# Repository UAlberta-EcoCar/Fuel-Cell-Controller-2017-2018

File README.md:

# Fuel-Cell-Controller-2017-2018

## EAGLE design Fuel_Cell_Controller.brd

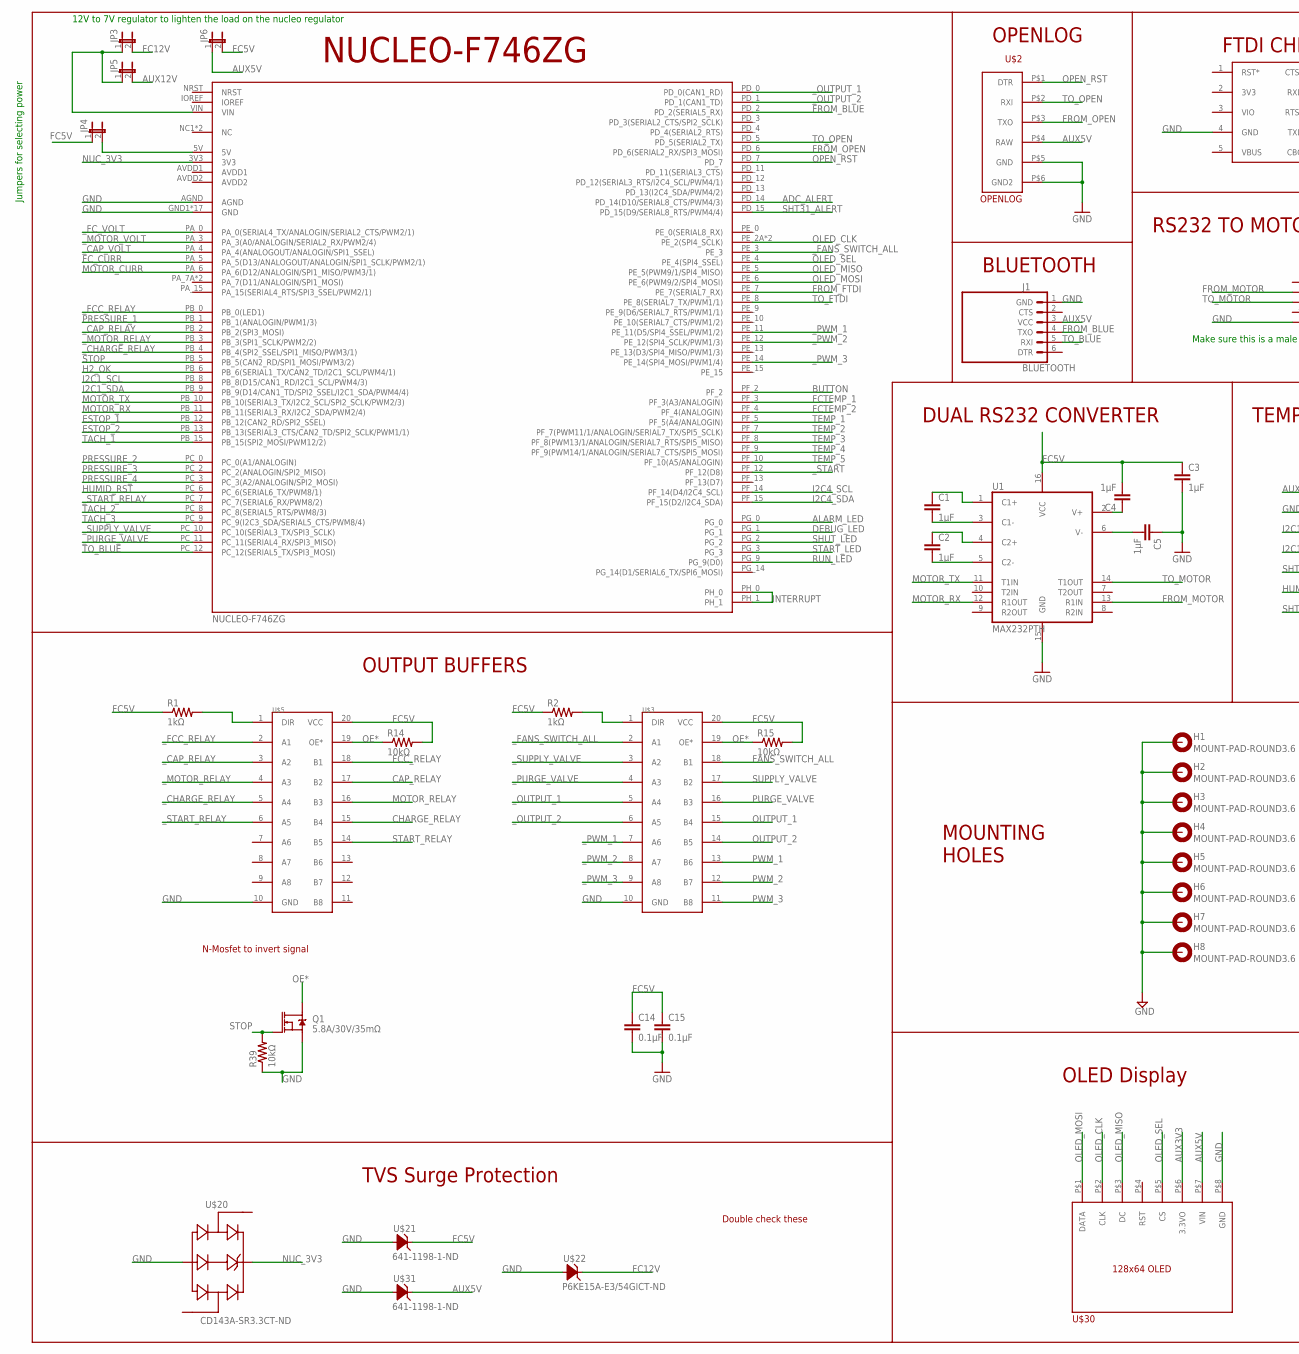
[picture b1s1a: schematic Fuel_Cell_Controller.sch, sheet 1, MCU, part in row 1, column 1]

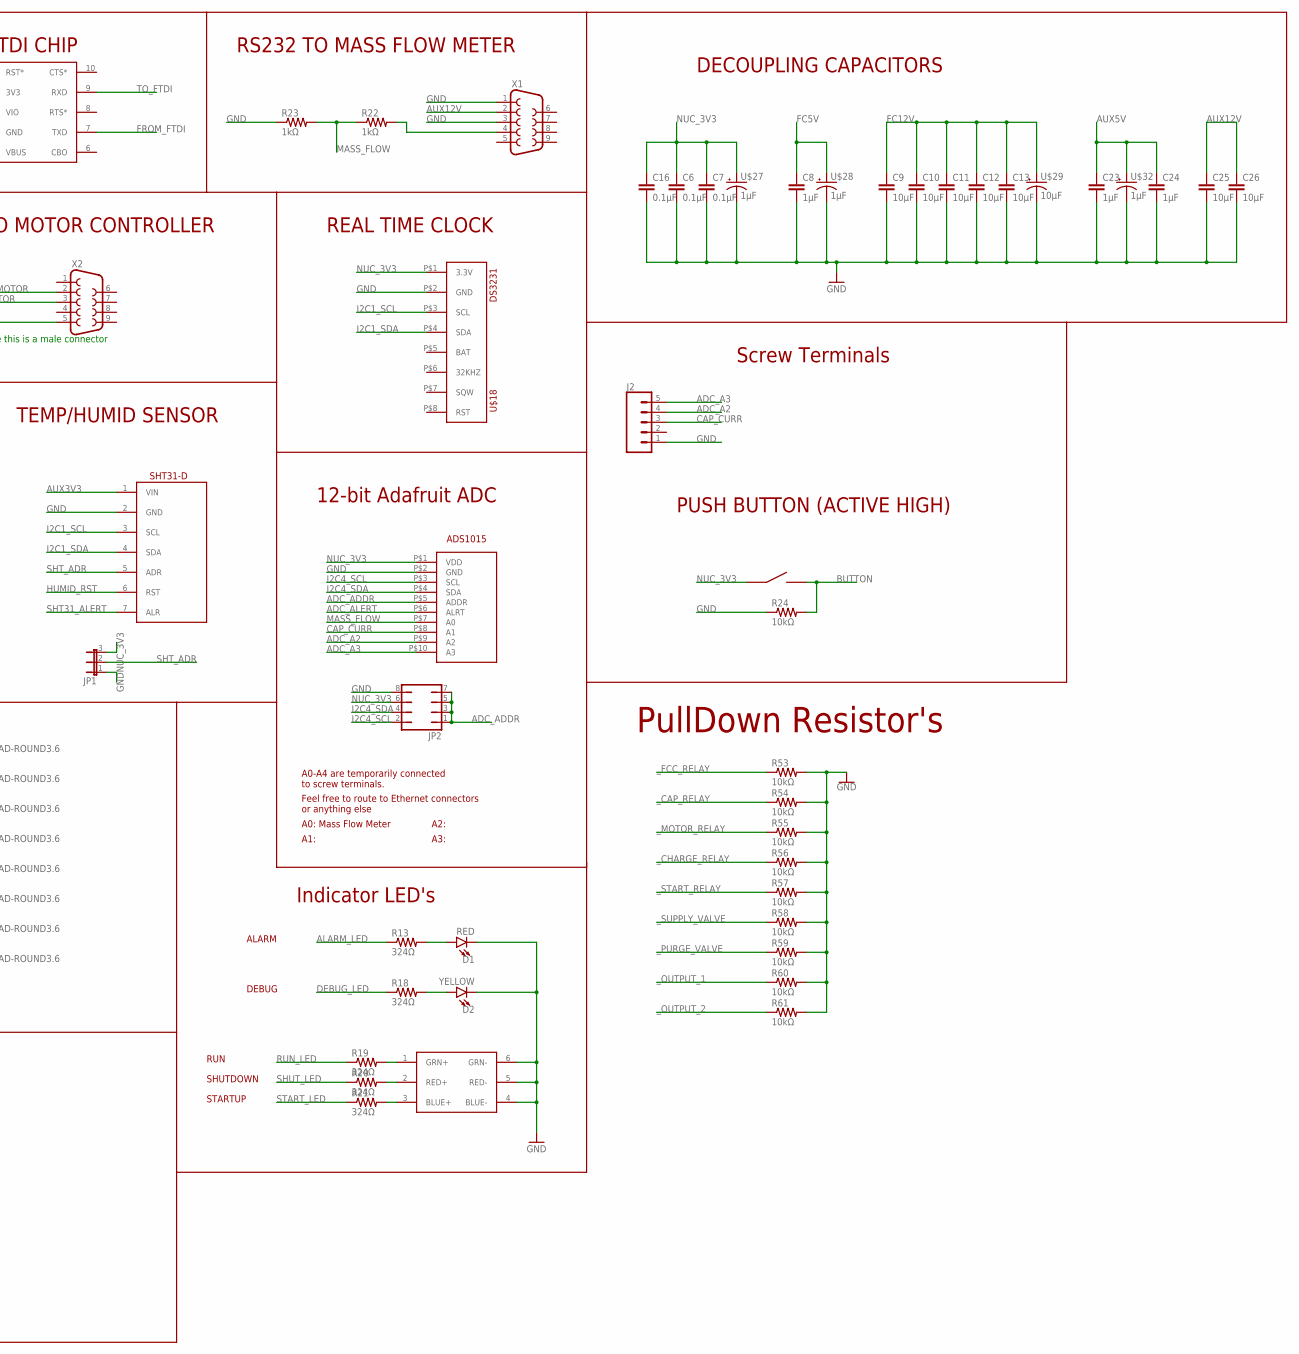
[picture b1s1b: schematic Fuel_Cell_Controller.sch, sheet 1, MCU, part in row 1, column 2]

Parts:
C1, C2, C3, C4, C5, C8, C23, C24: 1µF; 0805
C6, C7, C14, C15, C16: 0.1µF; 0805
C9, C10, C11, C12, C13, C25, C26: 10µF; 0805
D1: RED; LED-1206
D2: YELLOW; LED-1206
H1, H2, H3, H4, H5, H6, H7, H8: MOUNT-PAD-ROUND3.6; 3,6-PAD
J1: BLUETOOTH; 1X06BLUETOOTH
J2: CONN_05SCREW; SCREWTERMINAL-3.5MM-5
JP1: JP2E; JP2
JP2: JP4Q
JP3, JP4, JP5, JP6: JP1E; JP1
Q1: 5.8A/30V/35mΩ; SOT23-3
R1, R2, R22, R23: 1kΩ; 0805
R13, R18, R19, R20, R21: 324Ω; 0805
R14, R15, R24, R39, R53, R54, R55, R56, R57, R58, R59, R60, R61: 10kΩ; 0805
SHTSENSOR: SHT31-DIS; 1X07-SHT31-DIS
U1: MAX232PTH; DIL16
U$1: NUCLEO-F746ZGNUCLEO-F746ZG; NUCLEO-F746ZG
U$2: OPENLOG
U$3, U$5: SN74LVC245AN; DIL20
U$10: UMFT234XF
U$18: DS3231
U$19: ADS1015
U$20: CD143A-SR3.3CT-ND; SOT143_AVAGO
U$21, U$31: 641-1198-1-ND; SOT23
U$22: P6KE15A-E3/54GICT-ND; DO-204AC
U$25: 5060BRG45060BRG4; 5060BRG4
U$26: EG4621CT-ND
U$27, U$28, U$32: 1µF; PANASONIC_D
U$29: 10µF; PANASONIC_D
U$30: ADAFRUITOLED; 1X08OLED
X1, X2: F09HP

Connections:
ADC_A2: J2.4, U$19.P$9 (A2)
ADC_A3: J2.5, U$19.P$10 (A3)
ADC_ADDR: JP2.1, JP2.3, JP2.5, JP2.7, U$19.P$5 (ADDR)
ADC_ALERT: U$1.PD_14 (PD_14(D10/SERIAL8_CTS/PWM4/3)), U$19.P$6 (ALRT)
ALARM_LED: R13.1, U$1.PG_0
AUX3V3: SHTSENSOR.1 (VIN), U$30.P$6 (3.3VO)
AUX5V: C23.1, C24.1, J1.3 (VCC), JP6.1, U$2.P$4 (RAW), U$30.P$7 (VIN), U$31.C, U$32.+; also elsewhere on the board
AUX12V: C25.1, C26.1, JP5.2, X1.2; also elsewhere on the board
BUTTON: R24.2, U$1.PF_2, U$26.P$3, U$26.P$4
CAP_CURR: J2.3, U$19.P$8 (A1); also elsewhere on the board
CAP_RELAY: U$5.17 (B2); also elsewhere on the board
CHARGE_RELAY: U$5.15 (B4); also elsewhere on the board
DEBUG_LED: R18.1, U$1.PG_1
ESTOP_1: U$1.PB_12 (PB_12(CAN2_RD/SPI2_SSEL)); also elsewhere on the board
ESTOP_2: U$1.PB_13 (PB_13(SERIAL3_CTS/CAN2_TD/SPI2_SCLK/PWM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); also elsewhere on the board
FANS_SWITCH_ALL: U$3.18 (B1); also elsewhere on the board
FC5V: C3.1, C4.2, C8.1, C14.1, C15.1, JP4.1, JP6.2, R1.1, R2.1, R14.2, R15.2, U1.16 (VCC), U$3.20 (VCC), U$5.20 (VCC), U$21.C, U$28.+; also elsewhere on the board
FC12V: C9.1, C10.1, C11.1, C12.1, C13.1, JP3.2, U$22.CATHODE (C), U$29.+; also elsewhere on the board
FCC_RELAY: U$5.18 (B1); also elsewhere on the board
FCTEMP_1: U$1.PF_3 (PF_3(A3/ANALOGIN)); also elsewhere on the board
FCTEMP_2: U$1.PF_4 (PF_4(ANALOGIN)); also elsewhere on the board
FC_CURR: U$1.PA_5 (PA_5(D13/ANALOGOUT/ANALOGIN/SPI1_SCLK/P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); also elsewhere on the board
FROM_BLUE: J1.4 (TXO), U$1.PD_2 (PD_2(SERIAL5_RX))
FROM_FTDI: U$1.PE_7 (PE_7(SERIAL7_RX)), U$10.7 (TXD)
FROM_MOTOR: U1.13 (R1IN), X2.2
FROM_OPEN: U$1.PD_6 (PD_6(SERIAL2_RX/SPI3_MOSI)), U$2.P$3 (TXO)
GND: C3.2, C5.1, C6.2, C7.2, C8.2, C9.2, C10.2, C11.2, C12.2, C13.2, C14.2, C15.2, C16.2, C23.2, C24.2, C25.2, C26.2, D1.C, D2.C, H1.B3,6, H2.B3,6, H3.B3,6, H4.B3,6, H5.B3,6, H6.B3,6, H7.B3,6, H8.B3,6, J1.1 (GND), J2.1, JP1.1, JP2.8, Q1.2 (S), R23.1, R24.1, R39.1, R53.2, R54.2, R55.2, R56.2, R57.2, R58.2, R59.2, R60.2, R61.2, SHTSENSOR.2 (GND), U1.15 (GND), U$1.AGND, U$1.GND1 (GND), U$1.GND2 (GND), U$1.GND3 (GND), U$1.GND4 (GND), U$1.GND5 (GND), U$1.GND6 (GND), U$1.GND7 (GND), U$1.GND8 (GND), U$1.GND9 (GND), U$1.GND10 (GND), U$1.GND11 (GND), U$1.GND12 (GND), U$1.GND13 (GND), U$1.GND14 (GND), U$1.GND15 (GND), U$1.GND16 (GND), U$1.GND17 (GND), U$2.P$5 (GND), U$2.P$6 (GND2), U$3.10 (GND), U$5.10 (GND), U$10.4 (GND), U$18.P$2 (GND), U$19.P$2 (GND), U$20.GND, U$21.A1 (A), U$21.A2 (A), U$22.ANODE (A), U$25.4 (BLUE-), U$25.5 (RED-), U$25.6 (GRN-), U$27.-, U$28.-, U$29.-, U$30.P$8 (GND), U$31.A1 (A), U$31.A2 (A), U$32.-, X1.1, X1.3, X2.5; also elsewhere on the board
H2_OK: U$1.PB_6 (PB_6(SERIAL1_TX/CAN2_TD/I2C1_SCL/PWM4/1)); also elsewhere on the board
HUMID_RST: SHTSENSOR.6 (RST), U$1.PC_6 (PC_6(SERIAL6_TX/PWM8/1))
I2C1_SCL: SHTSENSOR.3 (SCL), U$1.PB_8 (PB_8(D15/CAN1_RD/I2C1_SCL/PWM4/3)), U$18.P$3 (SCL)
I2C1_SDA: SHTSENSOR.4 (SDA), U$1.PB_9 (PB_9(D14/CAN1_TD/SPI2_SSEL/I2C1_SDA/PWM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), U$18.P$4 (SDA)
I2C4_SCL: JP2.2, U$1.PF_14 (PF_14(D4/I2C4_SCL)), U$19.P$3 (SCL)
I2C4_SDA: JP2.4, U$1.PF_15 (PF_15(D2/I2C4_SDA)), U$19.P$4 (SDA)
INTERRUPT: U$1.PH_0, U$1.PH_1
MASS_FLOW: R22.1, R23.2, U$19.P$7 (A0)
MOTOR_CURR: U$1.PA_6 (PA_6(D12/ANALOGIN/SPI1_MISO/PWM3/1)); also elsewhere on the board
MOTOR_RELAY: U$5.16 (B3); also elsewhere on the board
MOTOR_RX: U1.12 (R1OUT), U$1.PB_11 (PB_11(SERIAL3_RX/I2C2_SDA/PWM2/4))
MOTOR_TX: U1.11 (T1IN), U$1.PB_10 (PB_10(SERIAL3_TX/I2C2_SCL/SPI2_SCLK/PWM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)
unnamed: JP4.2, U$1.5V
unnamed: C1.1, U1.1 (C1+)
unnamed: C1.2, U1.3 (C1-)
unnamed: C2.1, U1.4 (C2+)
unnamed: C2.2, U1.5 (C2-)
unnamed: C4.1, U1.2 (V+)
unnamed: C5.2, U1.6 (V-)
unnamed: R2.2, U$3.1 (DIR)
unnamed: R1.2, U$5.1 (DIR)
unnamed: R22.2, X1.4
unnamed: D1.A, R13.2
unnamed: D2.A, R18.2
unnamed: R19.2, U$25.1 (GRN+)
unnamed: R20.2, U$25.2 (RED+)
unnamed: R21.2, U$25.3 (BLUE+)
NUC_3V3: C6.1, C7.1, C16.1, JP1.3, JP2.6, U$1.3V3, U$18.P$1 (3.3V), U$19.P$1 (VDD), U$20.VDD, U$26.P$1, U$26.P$2, U$27.+; also elsewhere on the board
OE*: Q1.3 (D), R14.1, R15.1, U$3.19 (OE*), U$5.19 (OE*)
OLED_CLK: U$1.PE_2A (PE_2(SPI4_SCLK)), U$1.PE_2B (PE_2(SPI4_SCLK)), U$30.P$2 (CLK)
OLED_MISO: U$1.PE_5 (PE_5(PWM9/1/SPI4_MISO)), U$30.P$3 (DC)
OLED_MOSI: U$1.PE_6 (PE_6(PWM9/2/SPI4_MOSI)), U$30.P$1 (DATA)
OLED_SEL: U$1.PE_4 (PE_4(SPI4_SSEL)), U$30.P$5 (CS)
OPEN_RST: U$1.PD_7, U$2.P$1 (DTR)
OUTPUT_1: U$3.15 (B4); also elsewhere on the board
OUTPUT_2: U$3.14 (B5); also elsewhere on the board
PRESSURE_1: U$1.PB_1 (PB_1(ANALOGIN/PWM1/3)); also elsewhere on the board
PRESSURE_2: U$1.PC_0 (PC_0(A1/ANALOGIN)); also elsewhere on the board
PRESSURE_3: U$1.PC_2 (PC_2(ANALOGIN/SPI2_MISO)); also elsewhere on the board
PRESSURE_4: U$1.PC_3 (PC_3(A2/ANALOGIN/SPI2_MOSI)); also elsewhere on the board
PURGE_VALVE: U$3.16 (B3); also elsewhere on the board
PWM_1: U$3.13 (B6); also elsewhere on the board
PWM_2: U$3.12 (B7); also elsewhere on the board
PWM_3: U$3.11 (B8); also elsewhere on the board
RUN_LED: R19.1, U$1.PG_9 (PG_9(D0))
SHT31_ALERT: SHTSENSOR.7 (ALR), U$1.PD_15 (PD_15(D9/SERIAL8_RTS/PWM4/4))
SHT_ADR: JP1.2, SHTSENSOR.5 (ADR)
SHUT_LED: R20.1, U$1.PG_2
START_LED: R21.1, U$1.PG_3
START_RELAY: U$5.14 (B5); also elsewhere on the board
STOP: Q1.1 (G), R39.2, U$1.PB_5 (PB_5(CAN2_RD/SPI1_MOSI/PWM3/2)); also elsewhere on the board
SUPPLY_VALVE: U$3.17 (B2); also elsewhere on the board
TACH_1: U$1.PB_15 (PB_15(SPI2_MOSI/PWM12/2)); also elsewhere on the board
TACH_2: U$1.PC_8 (PC_8(SERIAL5_RTS/PWM8/3)); also elsewhere on the board
TACH_3: U$1.PC_9 (PC_9(I2C3_SDA/SERIAL5_CTS/PWM8/4)); also elsewhere on the board
TEMP_1: U$1.PF_5 (PF_5(A4/ANALOGIN)); also elsewhere on the board
TEMP_2: U$1.PF_7 (PF_7(PWM11/1/ANALOGIN/SERIAL7_TX/SPI5_S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); also elsewhere on the board
TEMP_3: U$1.PF_8 (PF_8(PWM13/1/ANALOGIN/SERIAL7_RTS/SPI5_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); also elsewhere on the board
TEMP_4: U$1.PF_9 (PF_9(PWM14/1/ANALOGIN/SERIAL7_CTS/SPI5_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); also elsewhere on the board
TEMP_5: U$1.PF_10 (PF_10(A5/ANALOGIN)); also elsewhere on the board
TO_BLUE: J1.5 (RXI), U$1.PC_12 (PC_12(SERIAL5_TX/SPI3_MOSI))
TO_FTDI: U$1.PE_8 (PE_8(SERIAL7_TX/PWM1/1)), U$10.9 (RXD)
TO_MOTOR: U1.14 (T1OUT), X2.3
TO_OPEN: U$1.PD_5 (PD_5(SERIAL2_TX)), U$2.P$2 (RXI)
VIN: JP3.1, JP5.1, U$1.VIN
_CAP_RELAY: R54.1, U$1.PB_2 (PB_2(SPI3_MOSI)), U$5.3 (A2)
_CAP_VOLT: U$1.PA_4 (PA_4(ANALOGOUT/ANALOGIN/SPI1_SSEL)); also elsewhere on the board
_CHARGE_RELAY: R56.1, U$1.PB_4 (PB_4(SPI2_SSEL/SPI1_MISO/PWM3/1)), U$5.5 (A4)
_FANS_SWITCH_ALL: U$1.PE_3, U$3.2 (A1)
_FCC_RELAY: R53.1, U$1.PB_0 (PB_0(LED1)), U$5.2 (A1)
_FC_VOLT: U$1.PA_0 (PA_0(SERIAL4_TX/ANALOGIN/SERIAL2_CTS/PW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); also elsewhere on the board
_MOTOR_RELAY: R55.1, U$1.PB_3 (PB_3(SPI1_SCLK/PWM2/2)), U$5.4 (A3)
_MOTOR_VOLT: U$1.PA_3 (PA_3(A0/ANALOGIN/SERIAL2_RX/PWM2/4)); also elsewhere on the board
_OUTPUT_1: R60.1, U$1.PD_0 (PD_0(CAN1_RD)), U$3.5 (A4)
_OUTPUT_2: R61.1, U$1.PD_1 (PD_1(CAN1_TD)), U$3.6 (A5)
_PURGE_VALVE: R59.1, U$1.PC_11 (PC_11(SERIAL4_RX/SPI3_MISO)), U$3.4 (A3)
_PWM_1: U$1.PE_11 (PE_11(D5/SPI4_SSEL/PWM1/2)), U$3.7 (A6)
_PWM_2: U$1.PE_12 (PE_12(SPI4_SCLK/PWM1/3)), U$3.8 (A7)
_PWM_3: U$1.PE_14 (PE_14(SPI4_MOSI/PWM1/4)), U$3.9 (A8)
_START: U$1.PF_12 (PF_12(D8)); also elsewhere on the board
_START_RELAY: R57.1, U$1.PC_7 (PC_7(SERIAL6_RX/PWM8/2)), U$5.6 (A5)
_SUPPLY_VALVE: R58.1, U$1.PC_10 (PC_10(SERIAL3_TX/SPI3_SCLK)), U$3.3 (A2)

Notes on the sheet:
NUCLEO-F746ZG
OPENLOG
BLUETOOTH
DUAL RS232 CONVERTER
RS232 TO MOTOR CONTROLLER
FTDI CHIP
TEMP/HUMID SENSOR
RS232 TO MASS FLOW METER
REAL TIME CLOCK
OUTPUT BUFFERS
12-bit Adafruit ADC
A0-A4 are temporarily connected to screw terminals.
Feel free to route to Ethernet connectors or anything else
A0: Mass Flow Meter
A1:
A2:
A3:
MOUNTING HOLES
Indicator LED's
TVS Surge Protection
DECOUPLING CAPACITORS
ALARM
Double check these
Screw Terminals
DEBUG
RUN
SHUTDOWN
STARTUP
PUSH BUTTON (ACTIVE HIGH)
OLED Display
N-Mosfet to invert signal
Jumpers for selecting power
12V to 7V regulator to lighten the load on the nucleo regulator
Make sure this is a male connector
PullDown Resistor's

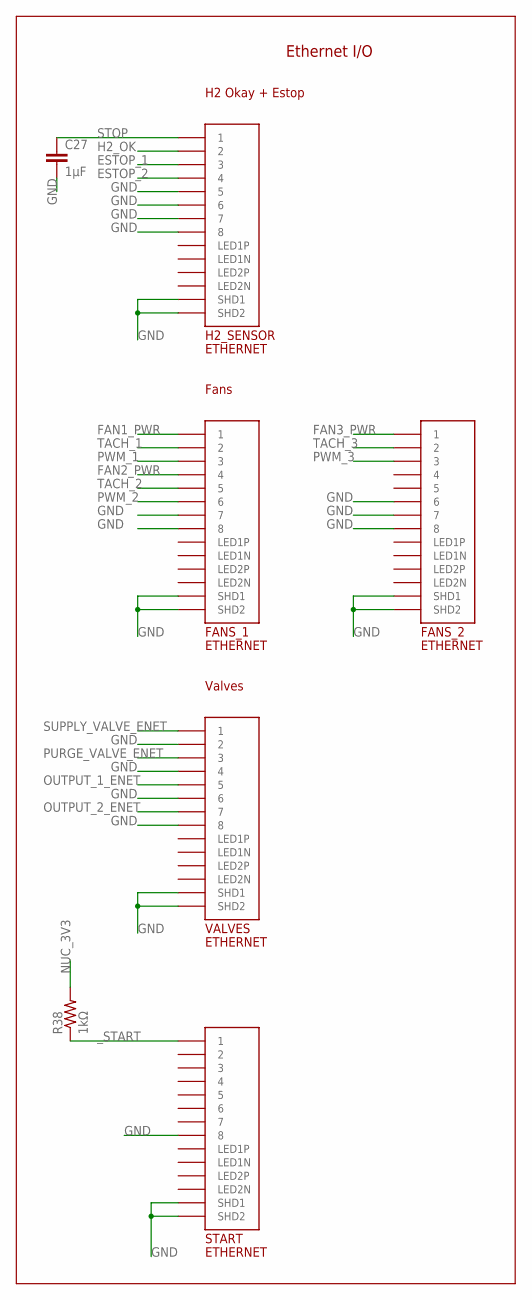
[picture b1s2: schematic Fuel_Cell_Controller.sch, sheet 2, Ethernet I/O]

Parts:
C27: 1µF; 0805
FANS_1, FANS_2: ETHERNET; A122645-ND
H2_SENSOR: ETHERNET; A122645-ND
R38: 1kΩ; 0805
START: ETHERNET; A122645-ND
VALVES: ETHERNET; A122645-ND

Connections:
ESTOP_1: H2_SENSOR.P$3 (3); also elsewhere on the board
ESTOP_2: H2_SENSOR.P$4 (4); also elsewhere on the board
FAN1_PWR: FANS_1.P$1 (1); also elsewhere on the board
FAN2_PWR: FANS_1.P$4 (4); also elsewhere on the board
FAN3_PWR: FANS_2.P$1 (1); also elsewhere on the board
GND: C27.2, FANS_1.P$7 (7), FANS_1.P$8 (8), FANS_1.P$13 (SHD1), FANS_1.P$14 (SHD2), FANS_2.P$6 (6), FANS_2.P$7 (7), FANS_2.P$8 (8), FANS_2.P$13 (SHD1), FANS_2.P$14 (SHD2), H2_SENSOR.P$5 (5), H2_SENSOR.P$6 (6), H2_SENSOR.P$7 (7), H2_SENSOR.P$8 (8), H2_SENSOR.P$13 (SHD1), H2_SENSOR.P$14 (SHD2), START.P$8 (8), START.P$13 (SHD1), START.P$14 (SHD2), VALVES.P$2 (2), VALVES.P$4 (4), VALVES.P$6 (6), VALVES.P$8 (8), VALVES.P$13 (SHD1), VALVES.P$14 (SHD2); also elsewhere on the board
H2_OK: H2_SENSOR.P$2 (2); also elsewhere on the board
NUC_3V3: R38.2; also elsewhere on the board
OUTPUT_1_ENET: VALVES.P$5 (5); also elsewhere on the board
OUTPUT_2_ENET: VALVES.P$7 (7); also elsewhere on the board
PURGE_VALVE_ENET: VALVES.P$3 (3); also elsewhere on the board
PWM_1: FANS_1.P$3 (3); also elsewhere on the board
PWM_2: FANS_1.P$6 (6); also elsewhere on the board
PWM_3: FANS_2.P$3 (3); also elsewhere on the board
STOP: C27.1, H2_SENSOR.P$1 (1); also elsewhere on the board
SUPPLY_VALVE_ENET: VALVES.P$1 (1); also elsewhere on the board
TACH_1: FANS_1.P$2 (2); also elsewhere on the board
TACH_2: FANS_1.P$5 (5); also elsewhere on the board
TACH_3: FANS_2.P$2 (2); also elsewhere on the board
_START: R38.1, START.P$1 (1); also elsewhere on the board

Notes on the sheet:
Ethernet I/O
Fans
Valves
H2 Okay + Estop

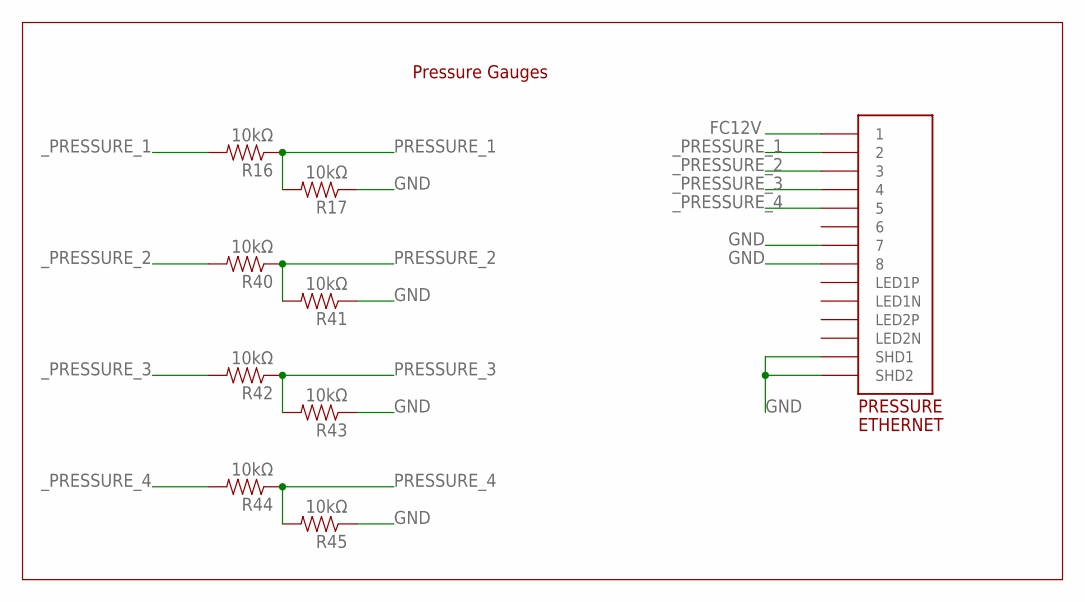
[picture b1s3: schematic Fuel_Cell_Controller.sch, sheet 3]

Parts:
PRESSURE: ETHERNET; A122645-ND
R16, R17, R40, R41, R42, R43, R44, R45: 10kΩ; 0805

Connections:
FC12V: PRESSURE.P$1 (1); also elsewhere on the board
GND: PRESSURE.P$7 (7), PRESSURE.P$8 (8), PRESSURE.P$13 (SHD1), PRESSURE.P$14 (SHD2), R17.1, R41.1, R43.1, R45.1; also elsewhere on the board
PRESSURE_1: R16.1, R17.2; also elsewhere on the board
PRESSURE_2: R40.1, R41.2; also elsewhere on the board
PRESSURE_3: R42.1, R43.2; also elsewhere on the board
PRESSURE_4: R44.1, R45.2; also elsewhere on the board
_PRESSURE_1: PRESSURE.P$2 (2), R16.2
_PRESSURE_2: PRESSURE.P$3 (3), R40.2
_PRESSURE_3: PRESSURE.P$4 (4), R42.2
_PRESSURE_4: PRESSURE.P$5 (5), R44.2

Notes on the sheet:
Pressure Gauges

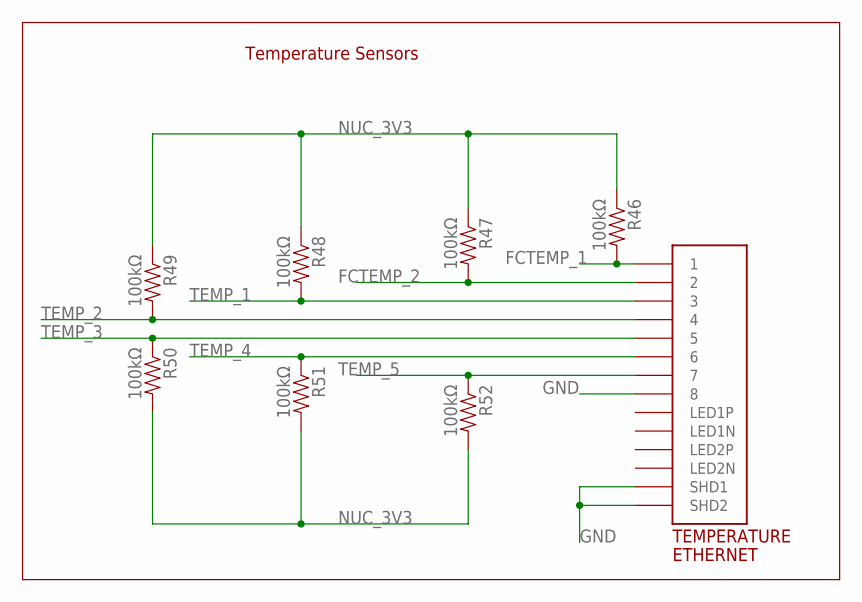
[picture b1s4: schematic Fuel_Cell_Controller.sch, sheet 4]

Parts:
R46, R47, R48, R49, R50, R51, R52: 100kΩ; 0805
TEMPERATURE: ETHERNET; A122645-ND

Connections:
FCTEMP_1: R46.2, TEMPERATURE.P$1 (1); also elsewhere on the board
FCTEMP_2: R47.2, TEMPERATURE.P$2 (2); also elsewhere on the board
GND: TEMPERATURE.P$8 (8), TEMPERATURE.P$13 (SHD1), TEMPERATURE.P$14 (SHD2); also elsewhere on the board
NUC_3V3: R46.1, R47.1, R48.1, R49.1, R50.2, R51.2, R52.2; also elsewhere on the board
TEMP_1: R48.2, TEMPERATURE.P$3 (3); also elsewhere on the board
TEMP_2: R49.2, TEMPERATURE.P$4 (4); also elsewhere on the board
TEMP_3: R50.1, TEMPERATURE.P$5 (5); also elsewhere on the board
TEMP_4: R51.1, TEMPERATURE.P$6 (6); also elsewhere on the board
TEMP_5: R52.1, TEMPERATURE.P$7 (7); also elsewhere on the board

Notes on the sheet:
Temperature Sensors

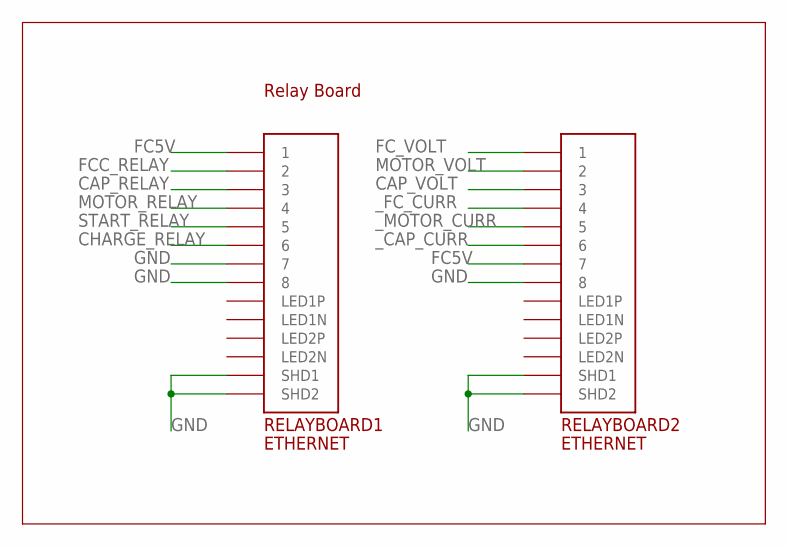
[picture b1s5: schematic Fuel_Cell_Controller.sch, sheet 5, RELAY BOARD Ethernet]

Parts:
RELAYBOARD1, RELAYBOARD2: ETHERNET; A122645-ND

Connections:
CAP_RELAY: RELAYBOARD1.P$3 (3); also elsewhere on the board
CAP_VOLT: RELAYBOARD2.P$3 (3); also elsewhere on the board
CHARGE_RELAY: RELAYBOARD1.P$6 (6); also elsewhere on the board
FC5V: RELAYBOARD1.P$1 (1), RELAYBOARD2.P$7 (7); also elsewhere on the board
FCC_RELAY: RELAYBOARD1.P$2 (2); also elsewhere on the board
FC_VOLT: RELAYBOARD2.P$1 (1); also elsewhere on the board
GND: RELAYBOARD1.P$7 (7), RELAYBOARD1.P$8 (8), RELAYBOARD1.P$13 (SHD1), RELAYBOARD1.P$14 (SHD2), RELAYBOARD2.P$8 (8), RELAYBOARD2.P$13 (SHD1), RELAYBOARD2.P$14 (SHD2); also elsewhere on the board
MOTOR_RELAY: RELAYBOARD1.P$4 (4); also elsewhere on the board
MOTOR_VOLT: RELAYBOARD2.P$2 (2); also elsewhere on the board
START_RELAY: RELAYBOARD1.P$5 (5); also elsewhere on the board
_CAP_CURR: RELAYBOARD2.P$6 (6); also elsewhere on the board
_FC_CURR: RELAYBOARD2.P$4 (4); also elsewhere on the board
_MOTOR_CURR: RELAYBOARD2.P$5 (5); also elsewhere on the board

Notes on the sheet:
Relay Board

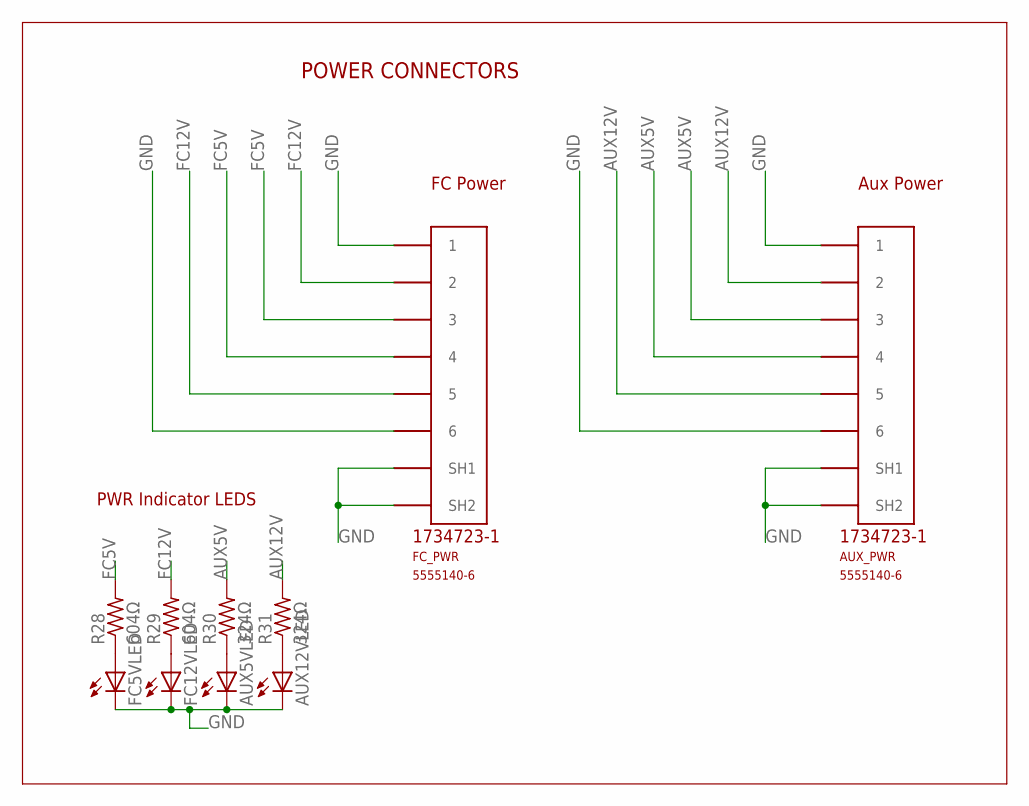
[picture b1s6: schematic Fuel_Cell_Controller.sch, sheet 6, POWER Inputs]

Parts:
AUX5VLED, AUX12VLED: LEDCHIP-LED0805; CHIP-LED0805
AUX_PWR: 5555140-6; 1734723-1_RJ11
FC5VLED, FC12VLED: LEDCHIP-LED0805; CHIP-LED0805
FC_PWR: 5555140-6; 1734723-1_RJ11
R28, R29: 604Ω; R0805
R30, R31: 324Ω; R0805

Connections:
AUX5V: AUX_PWR.3, AUX_PWR.4, R30.2; also elsewhere on the board
AUX12V: AUX_PWR.2, AUX_PWR.5, R31.2; also elsewhere on the board
FC5V: FC_PWR.3, FC_PWR.4, R28.2; also elsewhere on the board
FC12V: FC_PWR.2, FC_PWR.5, R29.2; also elsewhere on the board
GND: AUX5VLED.C, AUX12VLED.C, AUX_PWR.1, AUX_PWR.6, AUX_PWR.SH1, AUX_PWR.SH2, FC5VLED.C, FC12VLED.C, FC_PWR.1, FC_PWR.6, FC_PWR.SH1, FC_PWR.SH2; also elsewhere on the board
unnamed: FC5VLED.A, R28.1
unnamed: FC12VLED.A, R29.1
unnamed: AUX5VLED.A, R30.1
unnamed: AUX12VLED.A, R31.1

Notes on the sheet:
FC Power
Aux Power
POWER CONNECTORS
PWR Indicator LEDS

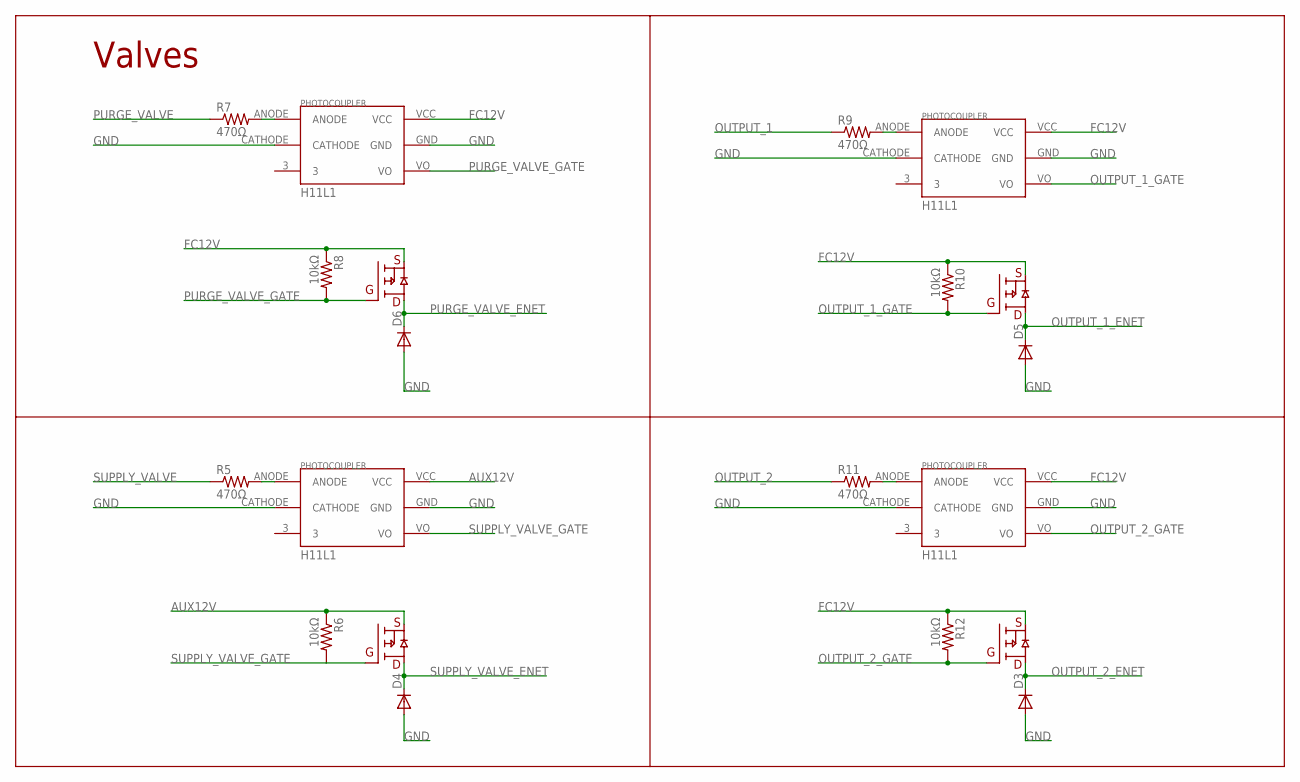
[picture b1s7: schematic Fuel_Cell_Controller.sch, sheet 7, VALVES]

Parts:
D3, D4, D5, D6: DIODE-DO214AC; DO214AC
R5, R7, R9, R11: 470Ω; 0805
R6, R8, R10, R12: 10kΩ; 0805
U$6, U$11, U$14, U$16: H11L1H11L1; H11L1
U$12, U$13, U$15, U$17: DMP3056L-7DMP3056L-7; DMP3056L-7

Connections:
AUX12V: R6.1, U$6.VCC, U$12.S (SOURCE); also elsewhere on the board
FC12V: R8.1, R10.1, R12.1, U$11.VCC, U$13.S (SOURCE), U$14.VCC, U$15.S (SOURCE), U$16.VCC, U$17.S (SOURCE); also elsewhere on the board
GND: D3.A, D4.A, D5.A, D6.A, U$6.CATHODE, U$6.GND, U$11.CATHODE, U$11.GND, U$14.CATHODE, U$14.GND, U$16.CATHODE, U$16.GND; also elsewhere on the board
unnamed: R5.2, U$6.ANODE
unnamed: R7.2, U$11.ANODE
unnamed: R9.2, U$14.ANODE
unnamed: R11.2, U$16.ANODE
OUTPUT_1: R9.1; also elsewhere on the board
OUTPUT_1_ENET: D5.C, U$15.D (DRAIN); also elsewhere on the board
OUTPUT_1_GATE: R10.2, U$14.VO, U$15.G (GATE)
OUTPUT_2: R11.1; also elsewhere on the board
OUTPUT_2_ENET: D3.C, U$17.D (DRAIN); also elsewhere on the board
OUTPUT_2_GATE: R12.2, U$16.VO, U$17.G (GATE)
PURGE_VALVE: R7.1; also elsewhere on the board
PURGE_VALVE_ENET: D6.C, U$13.D (DRAIN); also elsewhere on the board
PURGE_VALVE_GATE: R8.2, U$11.VO, U$13.G (GATE)
SUPPLY_VALVE: R5.1; also elsewhere on the board
SUPPLY_VALVE_ENET: D4.C, U$12.D (DRAIN); also elsewhere on the board
SUPPLY_VALVE_GATE: R6.2, U$6.VO, U$12.G (GATE)

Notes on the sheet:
Valves

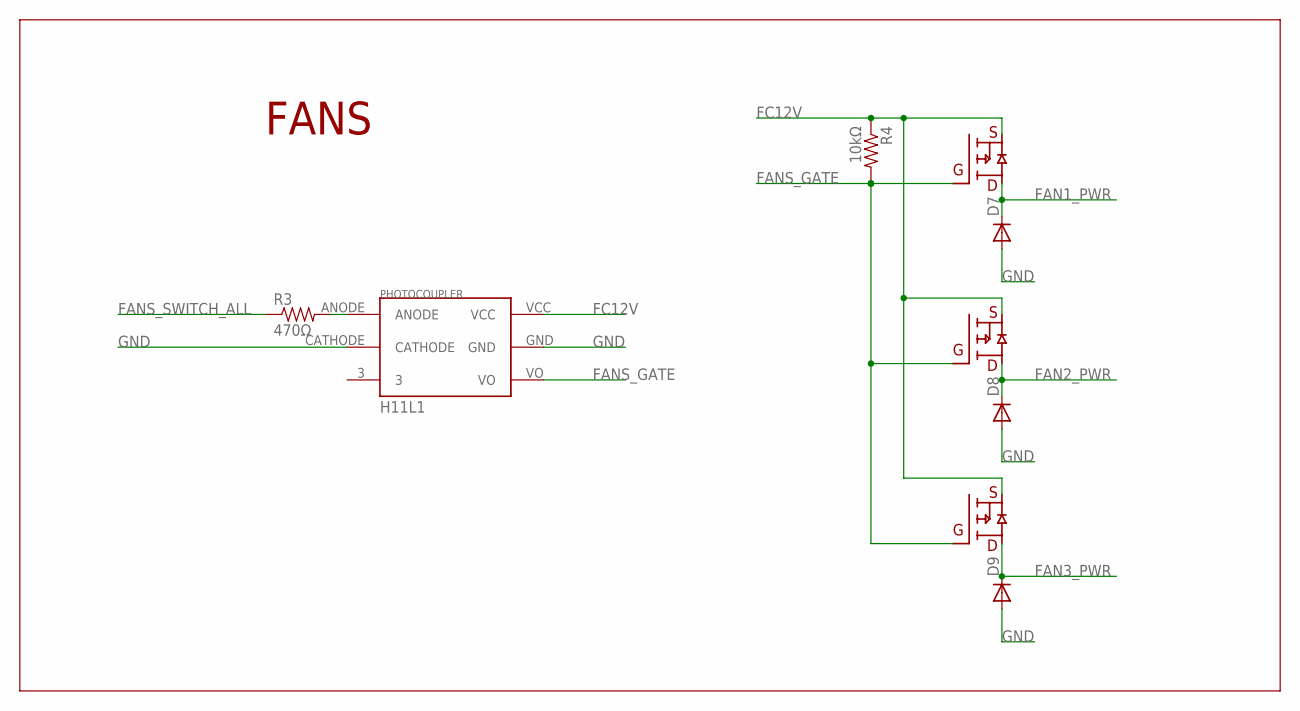
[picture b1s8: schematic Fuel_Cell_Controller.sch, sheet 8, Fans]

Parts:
D7, D8, D9: DIODE-DO214AC; DO214AC
R3: 470Ω; 0805
R4: 10kΩ; 0805
U$4: H11L1H11L1; H11L1
U$7, U$8, U$9: DMP3056L-7DMP3056L-7; DMP3056L-7

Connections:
FAN1_PWR: D7.C, U$7.D (DRAIN); also elsewhere on the board
FAN2_PWR: D8.C, U$8.D (DRAIN); also elsewhere on the board
FAN3_PWR: D9.C, U$9.D (DRAIN); also elsewhere on the board
FANS_GATE: R4.2, U$4.VO, U$7.G (GATE), U$8.G (GATE), U$9.G (GATE)
FANS_SWITCH_ALL: R3.1; also elsewhere on the board
FC12V: R4.1, U$4.VCC, U$7.S (SOURCE), U$8.S (SOURCE), U$9.S (SOURCE); also elsewhere on the board
GND: D7.A, D8.A, D9.A, U$4.CATHODE, U$4.GND; also elsewhere on the board
unnamed: R3.2, U$4.ANODE

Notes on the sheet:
FANS

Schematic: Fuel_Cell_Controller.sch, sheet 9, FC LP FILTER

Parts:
C17, C18, C19, C20, C21, C22: CAP0805; 0805
LP_FILTER_OP_AMP: TLV2404TLV2404; DIL14
R25, R26, R27: 0402
R32, R33, R34, R35, R36, R37: R-US_R0805; R0805

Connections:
CAP_CURR: C17.1, R36.2, R37.1; also elsewhere on the board
CAP_VOLT: LP_FILTER_OP_AMP.10 (3IN+); also elsewhere on the board
FC5V: LP_FILTER_OP_AMP.4 (VCC); also elsewhere on the board
FC_CURR: C19.1, R32.2, R33.1; also elsewhere on the board
FC_VOLT: LP_FILTER_OP_AMP.3 (1IN+); also elsewhere on the board
GND: C17.2, C18.2, C19.2, C20.2, C21.2, C22.2, LP_FILTER_OP_AMP.11 (GND), LP_FILTER_OP_AMP.12 (4IN+), LP_FILTER_OP_AMP.13 (4IN-), R33.2, R35.2, R37.2; also elsewhere on the board
MOTOR_CURR: C18.1, R34.2, R35.1; also elsewhere on the board
MOTOR_VOLT: LP_FILTER_OP_AMP.5 (2IN+); also elsewhere on the board
unnamed: LP_FILTER_OP_AMP.1 (1OUT), LP_FILTER_OP_AMP.2 (1IN-), R25.2
unnamed: LP_FILTER_OP_AMP.6 (2IN-), LP_FILTER_OP_AMP.7 (2OUT), R26.2
unnamed: LP_FILTER_OP_AMP.8 (3OUT), LP_FILTER_OP_AMP.9 (3IN-), R27.1
_CAP_CURR: R36.1; also elsewhere on the board
_CAP_VOLT: C22.1, R27.2; also elsewhere on the board
_FC_CURR: R32.1; also elsewhere on the board
_FC_VOLT: C20.1, R25.1; also elsewhere on the board
_MOTOR_CURR: R34.1; also elsewhere on the board
_MOTOR_VOLT: C21.1, R26.1; also elsewhere on the board

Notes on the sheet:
Current Sensors LP Filter and Voltage Divider
Voltages LP Filter

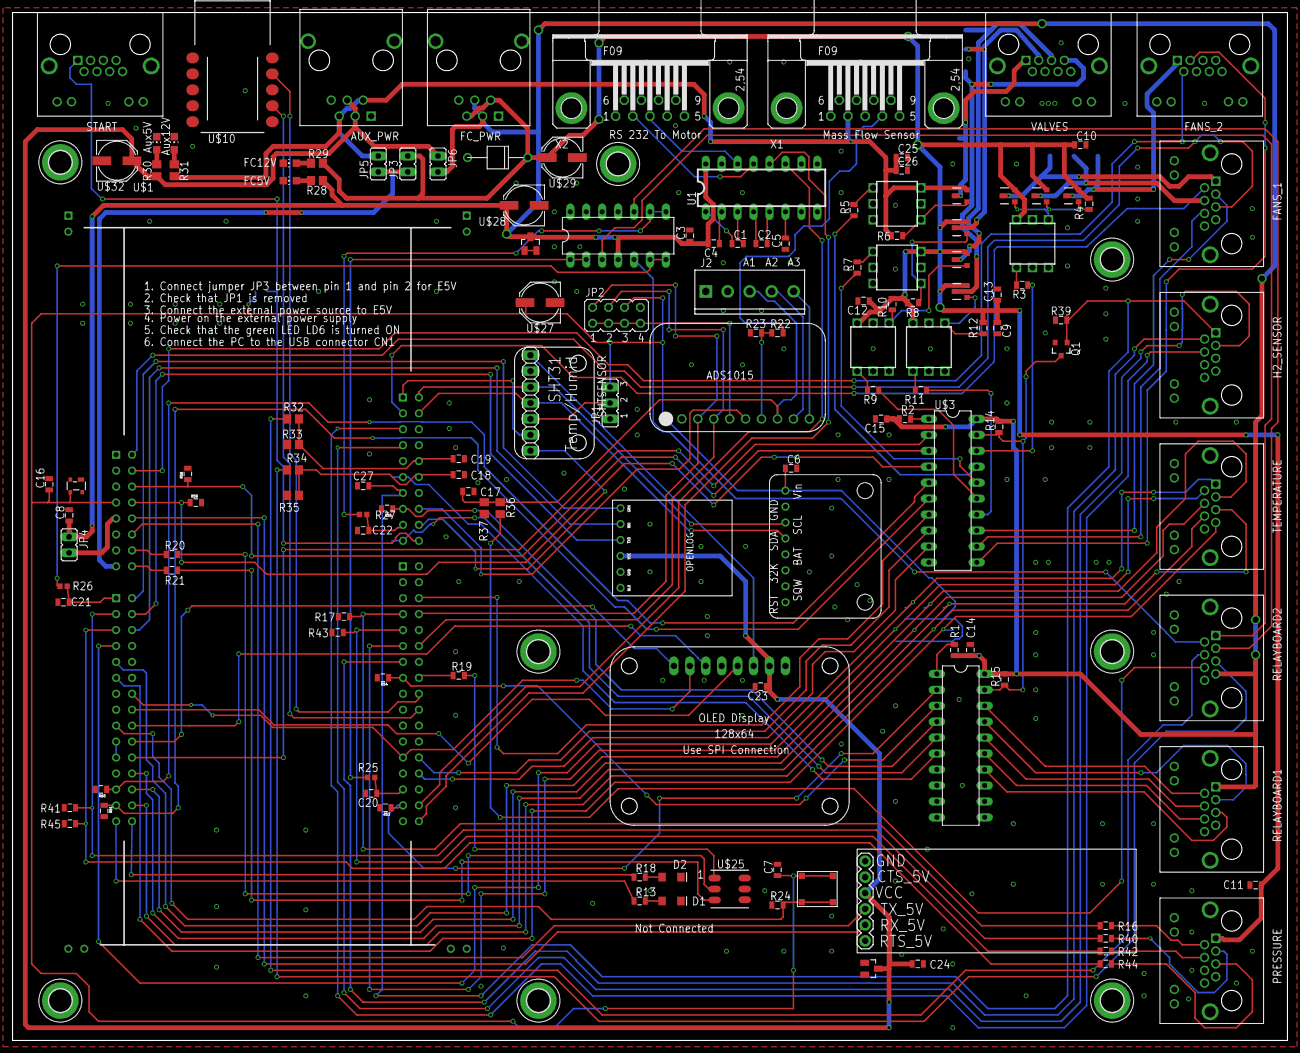
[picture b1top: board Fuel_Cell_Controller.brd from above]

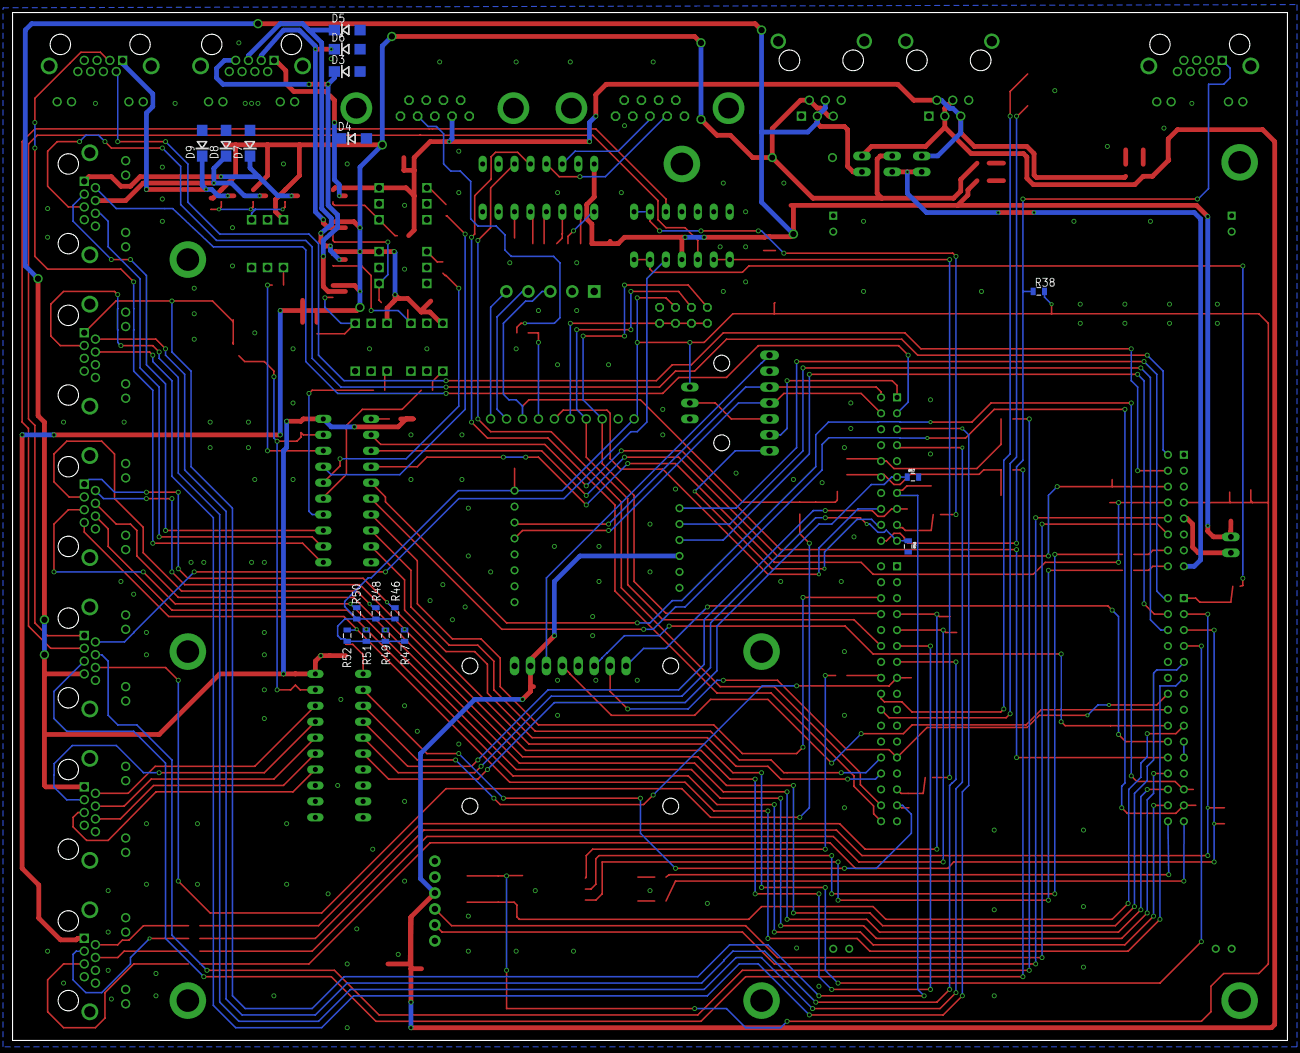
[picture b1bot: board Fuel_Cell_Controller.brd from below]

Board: 4 copper layers, 203.2 x 163.8 mm, 164 parts (17 on the bottom side), 143 nets.

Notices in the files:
parts and their libraries:
SparkFun-DigitalIC: Licensing: Creative Commons ShareAlike 4.0 International - https://creativecommons.org/licenses/by-sa/4.0
